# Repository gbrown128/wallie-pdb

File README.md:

# WALL-IE Power Distribution Board
Power Distribution Board for Team Congo's Bio Inspired Robots project, "WALL-IE".

Current Bio-Inspired Robots students please feel free to ask me questions about this design and options for your robot in the Issues section!

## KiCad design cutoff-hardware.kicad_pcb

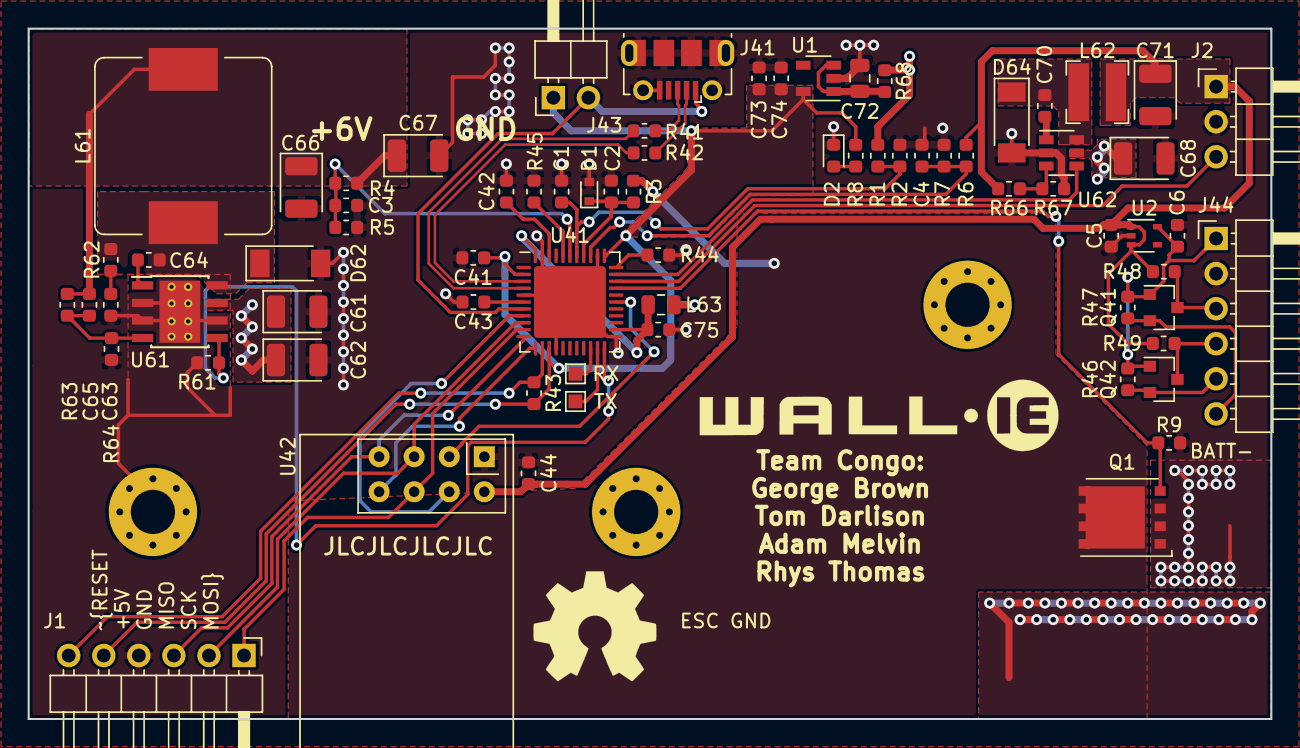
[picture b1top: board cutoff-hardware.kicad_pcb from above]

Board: 2 copper layers, 90.0 x 50.0 mm, 72 parts (0 on the bottom side), 47 nets.

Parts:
C1, C2, C3, C4, C41, C42, C44, C75: 100n; C_0603_1608Metric
C5, C6, C43, C73, C74: 1u; C_0603_1608Metric
C61, C62, C68: 10u; CP_EIA-3528-21_Kemet-B
C63: 270p; C_0603_1608Metric
C64, C70: 10n; C_0603_1608Metric
C65: 82p; C_0603_1608Metric
C66, C67, C71: 22u; CP_EIA-3528-12_Kemet-T
C72: 1u; C_0805_2012Metric
D1: 3V3; D_SOD-523
D2: KPT-1608EC; LED_0603_1608Metric
D62, D64: RB081LAM-20; D_SOD-128
J1, J44: Conn_01x06_Male; PinHeader_1x06_P2.54mm_Horizontal
J2: pyboard conn; PinHeader_1x03_P2.54mm_Horizontal
J41: USB_B_Micro; USB_Micro-B_Molex-105017-0001
J43: PROGRAM_PSU; PinHeader_1x02_P2.54mm_Horizontal
L61: 47u; L_Bourns_SRP1265
L62: 6.8u; L_Bourns-SRN4012
L63: 10u; L_0805_2012Metric
Q1: BSC009NE2LS; TDSON-8-1
Q41, Q42: BSS138; SOT-23
R1, R4, R7: 6k8; R_0603_1608Metric
R2, R44, R45: 1k; R_0603_1608Metric
R3, R5, R6: 4k7; R_0603_1608Metric
R8: 330; R_0603_1608Metric
R9, R43, R46, R47, R48, R49, R61: 10k; R_0603_1608Metric
R41, R42: 22; R_0603_1608Metric
R62: 240; R_0603_1608Metric
R63: 100k; R_0603_1608Metric
R64: 26.1k; R_0603_1608Metric
R66: 62k; R_0603_1608Metric
R67: 19.6k; R_0603_1608Metric
R68: 100; R_0603_1608Metric
RX: UART_RX; TestPoint_Pad_1.0x1.0mm
TX: UART_TX; TestPoint_Pad_1.0x1.0mm
U1: NCP718SN; SOT-23-5
U2: MIC5365-2.8YC5; SOT-353_SC-70-5
U41: ATmega32U4-MU; QFN-44-1EP_7x7mm_P0.5mm_EP5.2x5.2mm
U42: NRF24L01_Breakout; nRF24L01_Breakout
U61: RT2805A; TI_SO-PowerPAD-8_ThermalVias
U62: RT8259; SOT-23-6

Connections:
+2V8: C6.1, J44.1, Q41.1, Q42.1, R46.1, R47.1, U2.5
+3V3: C5.1, C44.1, C71.1, J2.1, L62.2, R6.1, R48.1, R49.1, R66.1, U2.1, U2.3, U42.2
+5V: C41.1, C73.1, C74.1, J1.5, J43.1, L63.1, R8.1, R43.2, U1.5, U41.2, U41.14, U41.34
+5VA: C75.1, L63.2, U41.24, U41.44
+6V: C65.1, C66.1, C67.1, L61.2, R4.1, R63.1
+BATT: C61.1, C62.1, C68.1, R1.1, R68.2, U61.7, U62.5
/2V8SCL: J44.6, Q41.2, R47.2
/2V8SDA: J44.5, Q42.2, R46.2
/3V3SCL: J44.3, Q41.3, R48.2
/3V3SDA: J44.4, Q42.3, R49.2
/3V3_sns: C4.1, R6.2, R7.1, U41.36
/6V_sns: C3.1, R4.2, R5.1, U41.39
/BATT_isns: C2.1, D1.1, R3.1, U41.37
/EMBEDDED_EN: U41.32, U62.4
/PWR_EN: Q1.4, R9.1, U41.30
/SERVO_EN: R61.1, U41.22, U61.5
/VBAT_sns: C1.1, R1.2, R2.1, U41.38
/microcontroller/AREF: C42.1, U41.42
/microcontroller/CE: U41.28, U42.3
/microcontroller/D+: J41.3, R41.2
/microcontroller/D-: J41.2, R42.2
/microcontroller/DIFF_GND_REF: R45.2, U41.40
/microcontroller/DuC+: R41.1, U41.4
/microcontroller/DuC-: R42.1, U41.3
/microcontroller/MISO: J1.3, U41.11, U42.7
/microcontroller/MOSI: J1.1, U41.10, U42.6
/microcontroller/RAD_IRQ: U41.12, U42.8
/microcontroller/RX: RX.1, U41.20
/microcontroller/SCK: J1.2, U41.9, U42.5
/microcontroller/TX: TX.1, U41.21
/microcontroller/USBREG: C43.1, U41.6
/microcontroller/~HWB: R44.2, U41.33
/microcontroller/~RESET: J1.6, R43.1, U41.13
/microcontroller/~SS: U41.8, U42.4
/power-supplies/3VBOOT: C70.1, U62.1
/power-supplies/3VFB: R66.2, R67.1, U62.3
/power-supplies/3VSW: C70.2, D64.1, L62.1, U62.6
/power-supplies/5VREG_PWR: C72.1, R68.1, U1.1, U1.3
/power-supplies/6VBOOT: C64.1, U61.1
/power-supplies/6VFB: C65.2, R63.2, R64.1, U61.4
/power-supplies/6VSNUB: C63.1, R62.2
/power-supplies/6VSW: C64.2, D62.1, L61.1, R62.1, U61.8
/pyboard_wdg: J2.3, U41.31
GND: C1.2, C2.2, C3.2, C4.2, C5.2, C6.2, C41.2, C42.2, C43.2, C44.2, C61.2, C62.2, C63.2, C66.2, C67.2, C68.2, C71.2, C72.2, C73.2, C74.2, C75.2, D1.2, D2.1, D62.2, D64.2, J1.4, J2.2, J41.5, J41.6, J44.2, Q1.1, Q1.2, Q1.3, R2.2, R5.2, R7.2, R9.2, R44.1, R45.1, R61.2, R64.2, R67.2, U1.2, U2.2, U41.5, U41.15, U41.23, U41.35, U41.43, U41.45, U42.1, U61.2, U61.3, U61.6, U61.9, U62.2
GNDPWR: Q1.5, R3.2
unnamed: D2.2, R8.2
VBUS: J41.1, J43.2, U41.7

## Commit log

2019-05-12 + Add reviewed version of the PDB design files. * Previous git history lives in the University of Southampton gitlab server!
2019-05-12 + Add the KiCAD gitignore. - Strip out old unwanted KiCAD files.
2019-05-12 Polish up the readme.
